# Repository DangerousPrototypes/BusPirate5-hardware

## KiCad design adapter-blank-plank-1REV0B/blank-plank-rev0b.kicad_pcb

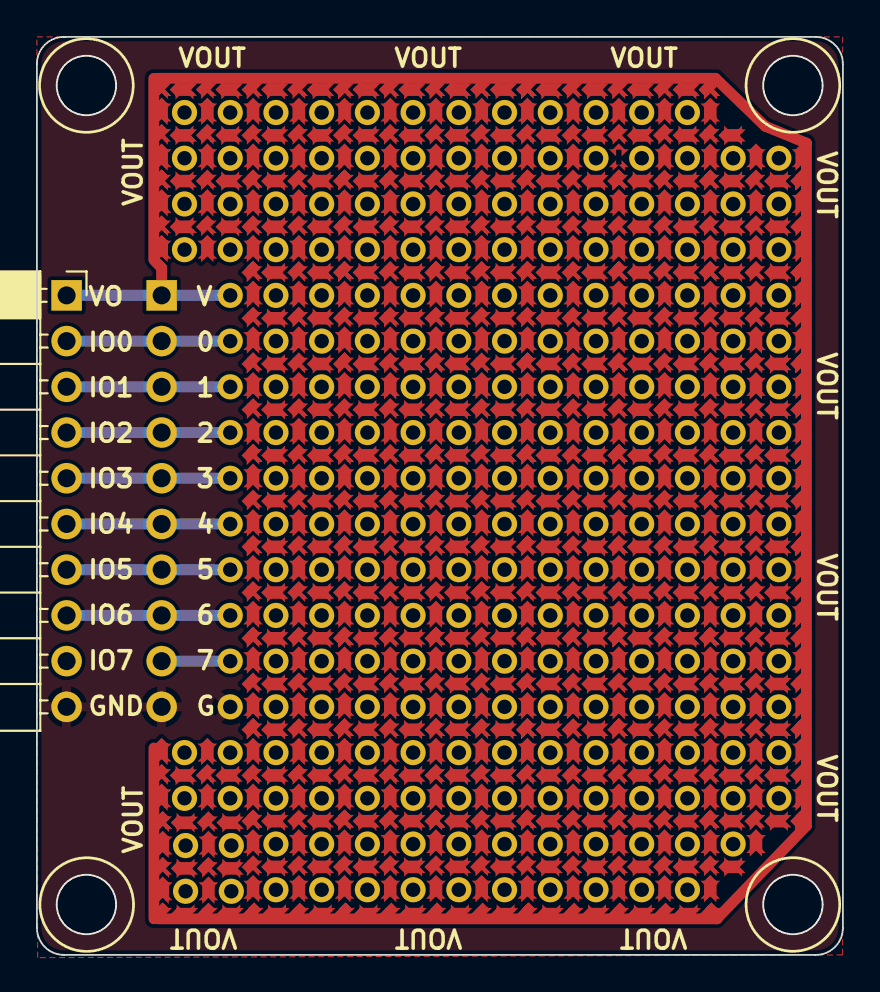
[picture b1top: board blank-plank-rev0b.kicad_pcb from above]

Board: 2 copper layers, 44.8 x 51.0 mm, 3 parts (0 on the bottom side), 10 nets.

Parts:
J2: Conn_01x10; PinSocket_1x10_P2.54mm_Horizontal
J3: Conn_01x10; PinHeader_1x10_P2.54mm_Vertical_No_Silk
J5: Conn_01x10; PinHeader_1x10_P2.54mm_Vertical_Reduced_2

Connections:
GND: J2.10, J3.10, J5.10
IO0: J2.2, J3.2, J5.2
IO1: J2.3, J3.3, J5.3
IO2: J2.4, J3.4, J5.4
IO3: J2.5, J3.5, J5.5
IO4: J2.6, J3.6, J5.6
IO5: J2.7, J3.7, J5.7
IO6: J2.8, J3.8, J5.8
IO7: J2.9, J3.9, J5.9
VOUT: J2.1, J3.1, J5.1

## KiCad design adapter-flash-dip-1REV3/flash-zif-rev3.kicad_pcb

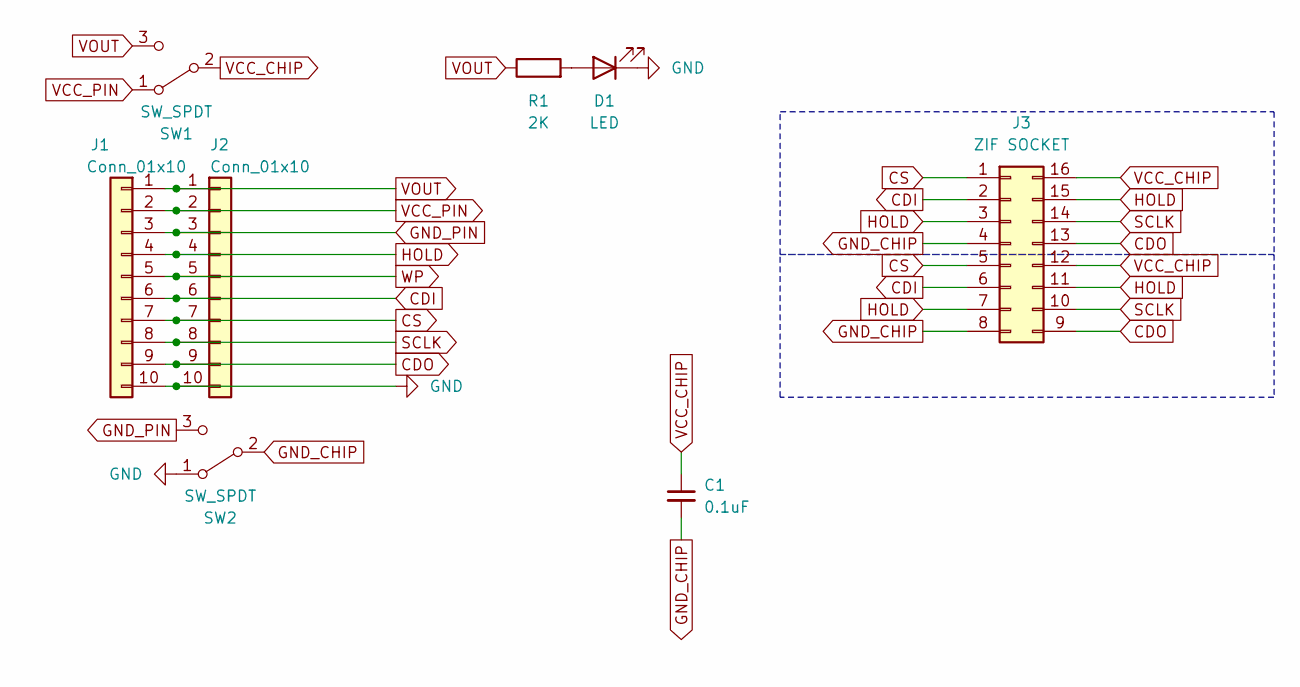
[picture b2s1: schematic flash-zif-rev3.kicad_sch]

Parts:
C1: 0.1uF; C_0805_2012Metric
D1: LED; LED_0805_2012Metric
J1: Conn_01x10; PinSocket_1x10_P2.54mm_Horizontal
J2: Conn_01x10; PinHeader_1x10_P2.54mm_Vertical
J3: ZIF SOCKET; DIP_Socket-16_W4.3_W5.08_W7.62_W10.16_W10.9_3M_216-3340-00-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
R1: 2K; R_0805_2012Metric
SW1, SW2: SW_SPDT; SW_SPDT_PCM12

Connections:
CDI: J1.6, J2.6, J3.2, J3.6
CDO: J1.9, J2.9, J3.9, J3.13
CS: J1.7, J2.7, J3.1, J3.5
GND: D1.1 (K), J1.10, J2.10, SW2.1 (A)
GND_CHIP: C1.2, J3.4, J3.8, SW2.2 (B)
GND_PIN: J1.3, J2.3, SW2.3 (C)
HOLD: J1.4, J2.4, J3.3, J3.7, J3.11, J3.15
unnamed: D1.2 (A), R1.2
SCLK: J1.8, J2.8, J3.10, J3.14
VCC_CHIP: C1.1, J3.12, J3.16, SW1.2 (B)
VCC_PIN: J1.2, J2.2, SW1.1 (A)
VOUT: J1.1, J2.1, R1.1, SW1.3 (C)
WP: J1.5, J2.5

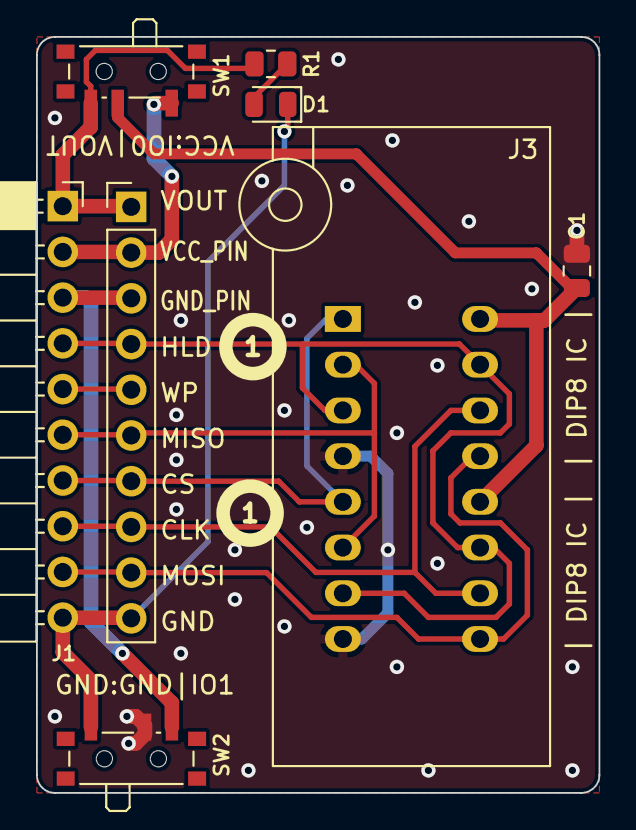
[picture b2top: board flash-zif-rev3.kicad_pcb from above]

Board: 2 copper layers, 31.2 x 42.0 mm, 8 parts (0 on the bottom side), 13 nets.

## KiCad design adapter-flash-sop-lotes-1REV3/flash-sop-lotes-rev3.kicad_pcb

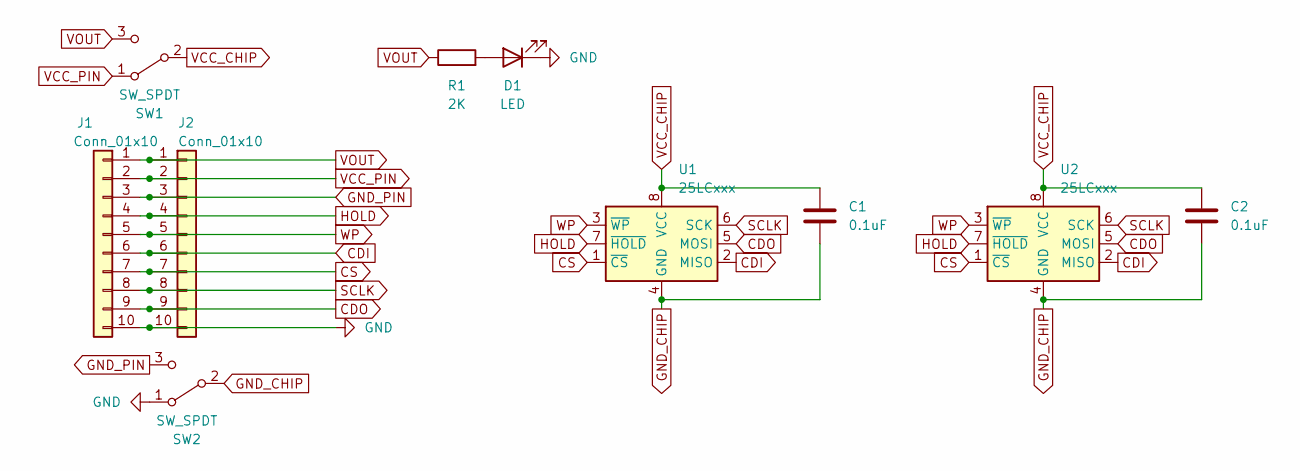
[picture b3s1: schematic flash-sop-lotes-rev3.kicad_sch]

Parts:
C1, C2: 0.1uF; C_0805_2012Metric
D1: LED; LED_0805_2012Metric
J1: Conn_01x10; PinSocket_1x10_P2.54mm_Horizontal
J2: Conn_01x10; PinHeader_1x10_P2.54mm_Vertical
R1: 2K; R_0805_2012Metric
SW1, SW2: SW_SPDT; SW_SPDT_PCM12
U1: 25LCxxx; ASPI0001-P001A
U2: 25LCxxx; ACA-SPI-004-K01

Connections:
CDI: J1.6, J2.6, U1.2 (MISO), U2.2 (MISO)
CDO: J1.9, J2.9, U1.5 (MOSI), U2.5 (MOSI)
CS: J1.7, J2.7, U1.1 (~CS), U2.1 (~CS)
GND: D1.1 (K), J1.10, J2.10, SW2.1 (A)
GND_CHIP: C1.2, C2.2, SW2.2 (B), U1.4 (GND), U2.4 (GND)
GND_PIN: J1.3, J2.3, SW2.3 (C)
HOLD: J1.4, J2.4, U1.7 (~HOLD), U2.7 (~HOLD)
unnamed: D1.2 (A), R1.2
SCLK: J1.8, J2.8, U1.6 (SCK), U2.6 (SCK)
VCC_CHIP: C1.1, C2.1, SW1.2 (B), U1.8 (VCC), U2.8 (VCC)
VCC_PIN: J1.2, J2.2, SW1.1 (A)
VOUT: J1.1, J2.1, R1.1, SW1.3 (C)
WP: J1.5, J2.5, U1.3 (~WP), U2.3 (~WP)

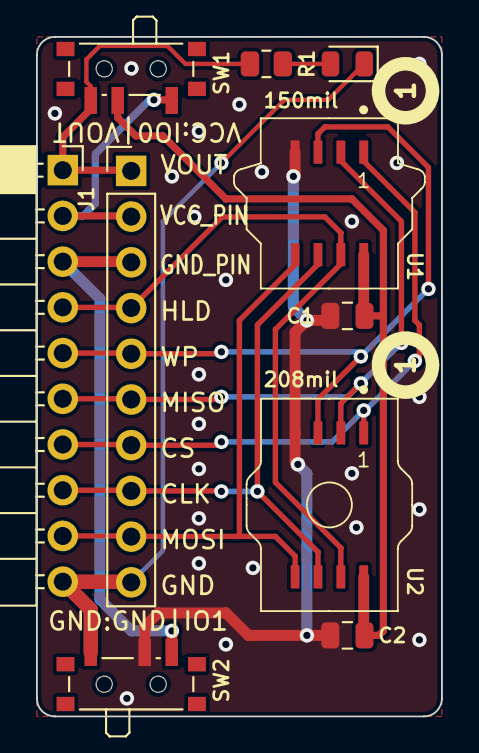
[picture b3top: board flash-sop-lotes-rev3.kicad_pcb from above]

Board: 2 copper layers, 22.5 x 37.8 mm, 10 parts (0 on the bottom side), 13 nets.

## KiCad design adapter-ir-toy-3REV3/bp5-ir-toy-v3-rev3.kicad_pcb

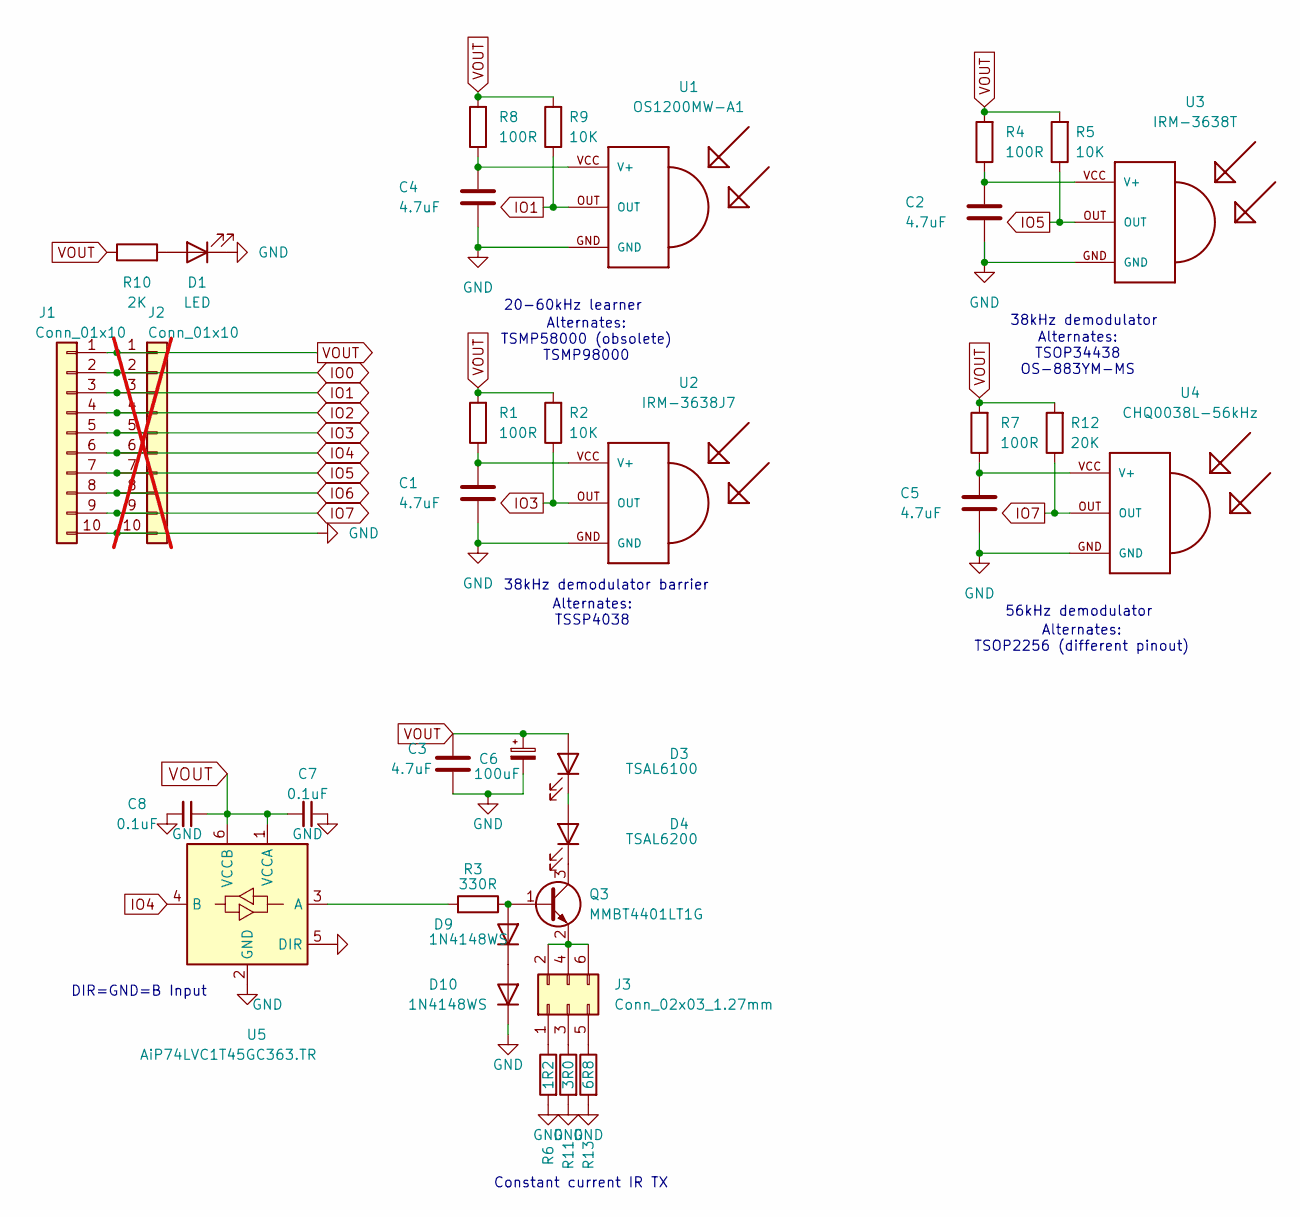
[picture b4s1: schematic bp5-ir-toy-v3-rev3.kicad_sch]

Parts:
C1, C2, C3, C4, C5: 4.7uF; C_0805_2012Metric
C6: 100uF; CP_EIA-3528-21_Kemet-B_Pad1.50x2.35mm_HandSolder
C7, C8: 0.1uF; C_0805_2012Metric
D1: LED; LED_0805_2012Metric
D3: TSAL6100; LED_D5.0mm_Horizontal_O1.27mm_Z3.0mm_IRGrey
D4: TSAL6200; LED_D5.0mm_Horizontal_O1.27mm_Z3.0mm_IRGrey
D9, D10: 1N4148WS; D_SOD-323F
J1: Conn_01x10; PinSocket_1x10_P2.54mm_Horizontal
J2: Conn_01x10; PinHeader_1x10_P2.54mm_Vertical; not fitted
J3: Conn_02x03_1.27mm; PinHeader_2x03_P1.27mm_Vertical
Q3: MMBT4401LT1G; SOT-23
R1, R4, R7, R8: 100R; R_0805_2012Metric
R2, R5, R9: 10K; R_0805_2012Metric
R3: 330R; R_0805_2012Metric
R6: 1R2; R_1206_3216Metric
R10: 2K; R_0805_2012Metric
R11: 3R0; R_1206_3216Metric
R12: 20K; R_0805_2012Metric
R13: 6R8; R_1206_3216Metric
U1: OS1200MW-A1; TSOP18XX
U2: IRM-3638J7; TSOP18XX
U3: IRM-3638T; TSOP18XX
U4: CHQ0038L-56kHz; TSOP18XX
U5: AiP74LVC1T45GC363.TR; SOT-363_SC-70-6

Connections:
GND: C1.2, C2.2, C3.2, C4.2, C5.2, C6.2, C7.1, C8.2, D1.1 (K), D10.1 (K), J1.10, J2.10, R6.2, R11.2, R13.2, U1.GND, U2.GND, U3.GND, U4.GND, U5.2 (GND), U5.5 (DIR)
IO0: J1.2, J2.2
IO1: J1.3, J2.3, R9.1, U1.OUT
IO2: J1.4, J2.4
IO3: J1.5, J2.5, R2.1, U2.OUT
IO4: J1.6, J2.6, U5.4 (B)
IO5: J1.7, J2.7, R5.1, U3.OUT
IO6: J1.8, J2.8
IO7: J1.9, J2.9, R12.1, U4.OUT
unnamed: D1.2 (A), R10.2
unnamed: D3.1 (K), D4.2 (A)
unnamed: D4.1 (K), Q3.3 (C)
unnamed: D9.2 (A), Q3.1 (B), R3.1
unnamed: D9.1 (K), D10.2 (A)
unnamed: J3.1, R6.1
unnamed: J3.2, J3.4, J3.6, Q3.2 (E)
unnamed: J3.3, R11.1
unnamed: J3.5, R13.1
unnamed: C4.1, R8.1, U1.VCC (V+)
unnamed: C1.1, R1.1, U2.VCC (V+)
unnamed: C2.1, R4.1, U3.VCC (V+)
unnamed: C5.1, R7.1, U4.VCC (V+)
unnamed: R3.2, U5.3 (A)
VOUT: C3.1, C6.1, C7.2, C8.1, D3.2 (A), J1.1, J2.1, R1.2, R2.2, R4.2, R5.2, R7.2, R8.2, R9.2, R10.1, R12.2, U5.1 (VCCA), U5.6 (VCCB)

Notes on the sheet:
Constant current IR TX
38kHz demodulator
56kHz demodulator
Alternates: TSMP58000 (obsolete) TSMP98000
38kHz demodulator barrier
Alternates: TSOP2256 (different pinout)
Alternates: TSOP34438 OS-883YM-MS
Alternates: TSSP4038
20-60kHz learner
DIR=GND=B Input

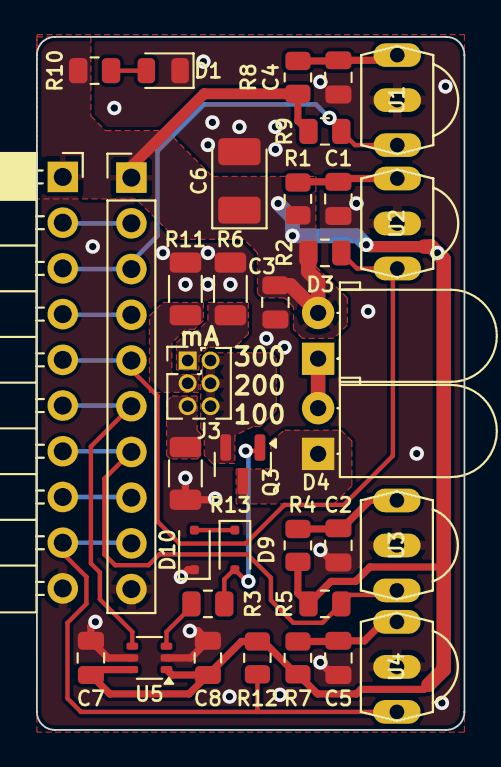
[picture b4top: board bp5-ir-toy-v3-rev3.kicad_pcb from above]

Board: 2 copper layers, 23.8 x 38.5 mm, 35 parts (0 on the bottom side), 24 nets.

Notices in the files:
adapter-blank-plank-1REV0B/blank-plank-rev0b.kicad_pcb:
Proto-Pattern CC-BY 4.0
